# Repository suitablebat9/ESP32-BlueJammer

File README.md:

# ESP32-BlueJammer

**Bluetooth / BLE / WiFi / 2.4GHz Jamming Board**

The **ESP32-BlueJammer** is a compact, feature-rich board designed to disrupt devices operating on the 2.4GHz frequency band. Powered by an ESP32 and an nRF24 module, it generates noise and sends excessive packets to interfere with:

- Bluetooth audio and data connections  
- WiFi networks  
- BLE (Bluetooth Low Energy) devices  
- RC drones and remotes  
- IoT gadgets and more

> ⚠️ **Disclaimer:** This project is based entirely on the work of [Emensta](https://github.com/EmenstaNougat/ESP32-BlueJammer). I created this PCB to make their project more plug-and-play. All credit for the original firmware and research goes to them.

---

## 🔧 Features

- Toggleable on/off switch  
- Onboard momentary activation button  
- **`EXT Switch`** solder pads for external or wireless switch activation  
- **`EXT Power`** solder pads for external 5V power input  
  - (Polarity: **Left = GND**, **Right = 5V** with antennas facing away from you)  
- Combo firmware support – press the ESP32’s boot button while powered to cycle modes  
- **Blue jamming LED** shows active mode (can be disabled via jumper)  
- PH 2.0 battery connector (battery not included, connector provided)  
- USB Type-C power input on the board (not on the ESP32 directly)

---

## 🔄 LED Blink Mode Key

The **blue jamming LED** will blink to indicate the current active jamming mode on combo firmware:

- `1 blink` = **BT** (Bluetooth Classic)  
- `2 blinks` = **BLE** (Bluetooth Low Energy)  
- `3 blinks` = **WiFi**  
- `4 blinks` = **RC** (2.4GHz Drone/Remote)

The blink key is also printed on the right side of the board for quick reference.

---

## 🛰️ Mode Descriptions

| Mode               | Description                         | Frequency Range          |
|--------------------|-------------------------------------|--------------------------|
| **BT 80CH**        | Bluetooth Classic Jammer            | 2.402 – 2.480 GHz        |
| **BLE 40CH**       | Bluetooth Low Energy Jammer         | 2.400 – 2.4835 GHz       |
| **BT-BLE 40-80CH** | Classic BT + BLE Combo Jammer       | 2.400 – 2.4835 GHz       |
| **BT-WiFi 14-80CH**| Classic BT + WiFi Combo Jammer      | 2.400 – 2.4835 GHz       |
| **WiFi 14CH**      | WiFi Jammer                         | 2.400 – 2.4835 GHz       |
| **2.4GHz All**     | RC / Drone Jammer (CH 1–125)        | 2.400 – 2.525 GHz        |

---

## 🔌 Flashing the Firmware

You can easily flash your board using the browser-based [ESP32 BlueJammer Web Flasher](https://esp32-bluejammerflasher.pages.dev/) provided by Emensta.

### Steps:
1. Visit [ESP32-BlueJammerFlasher](https://esp32-bluejammerflasher.pages.dev/)
2. Choose the firmware type, "Generic"
3. Choose the firmware you want to flash
4. Connect your ESP32 via a data USB cable
5. Flash the firmware of your choice

> 💡 Tip: If flashing fails, make sure you’re using a data-capable USB cable and have the correct drivers installed for your ESP32.

---

## 🛒 Buy the Board

Want a fully assembled board? You can purchase one from my Tindie store here:  
👉 [PCB Studios on Tindie](https://www.tindie.com/products/pcb-studios/esp32-bluejammer/)

---

## 📦 What's Included

- Fully assembled **ESP32-BlueJammer PCB**
- PH 2.0 battery connector pre-installed
- Matching PH 2.0 connector for your battery (DIY soldering)
- Gerber files and schematic PDF (in this repo)

---

## ⚠️ Legal Notice

This project is for educational purposes only. Do not use this board to interfere with any wireless communications unless you have permission and are operating in a controlled, legal environment. You are solely responsible for what you do with this device.

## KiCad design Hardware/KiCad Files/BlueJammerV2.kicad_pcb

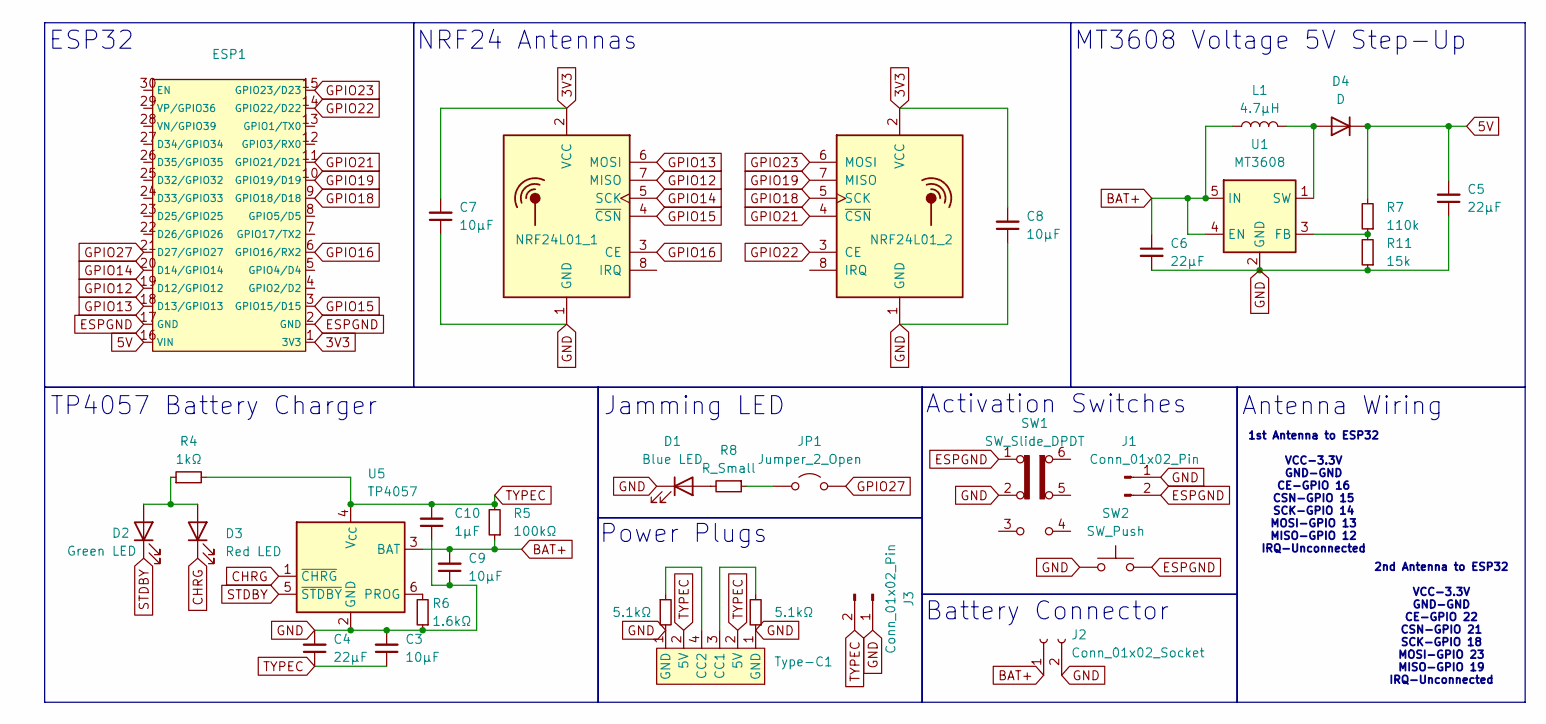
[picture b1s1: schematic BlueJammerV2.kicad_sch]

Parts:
C3, C7, C8, C9: 10µF; Cap_0805_2012Metric
C4, C5, C6: 22µF; Cap_0805_2012Metric
C10: 1µF; Cap_0805_2012Metric
D1: Blue LED; LED_1206_3216Metric_Pad1.42x1.75mm_HandSolder
D2: Green LED; LED_1206_3216Metric_Pad1.42x1.75mm_HandSolder
D3: Red LED; LED_1206_3216Metric_Pad1.42x1.75mm_HandSolder
D4: D; D_0805_2012Metric_Pad1.15x1.40mm_HandSolder
ESP1: 30 Pin ESP32 Dev Board
J1, J3: Conn_01x02_Pin; PinHeader_1x02_P2.54mm_Vertical
J2: Conn_01x02_Socket; JST_PH_S2B-PH-K_1x02_P2.00mm_Horizontal
JP1: Jumper_2_Open; TestPoint_2Pads_Pitch2.54mm_Drill0.8mm
L1: 4.7µH; L_0805_2012Metric_Pad1.15x1.40mm_HandSolder
R4: 1kΩ; R_1206_3216Metric
R5: 100kΩ; R_1206_3216Metric
R6: 1.6kΩ; R_1206_3216Metric
R7: 110k; R_0805_2012Metric_Pad1.20x1.40mm_HandSolder
R8: R_Small; R_1206_3216Metric
R9, R10: 5.1kΩ; R_1206_3216Metric
R11: 15k; R_0805_2012Metric_Pad1.20x1.40mm_HandSolder
SW1: SW_Slide_DPDT; MSS-22D18 Slide Switch
SW2: SW_Push; Button
Type-C1: SMD Type-C Port
U1: MT3608; SOT-23-6_Handsoldering
U2: NRF24L01_1; nRF24L01_Breakout
U3: NRF24L01_2; nRF24L01_Breakout
U5: TP4057; TSOT-23-6_HandSoldering

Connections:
3V3: C7.2, C8.2, ESP1.1 (3V3), U2.2 (VCC), U3.2 (VCC)
5V: C5.2, D4.1 (K), ESP1.16 (VIN), R7.2
BAT+: C6.1, C9.2, J2.1, L1.1, R5.1, U1.4 (EN), U1.5 (IN), U5.3 (BAT)
CHRG: D3.1 (K), U5.1 (~CHRG)
ESPGND: ESP1.2 (GND), ESP1.17 (GND), J1.2, SW1.1 (A), SW2.2
GND: C3.2, C4.2, C5.1, C6.2, C7.1, C8.1, C9.1, C10.1, D1.1 (K), J1.1, J2.2, J3.1, R6.1, R9.1, R10.2, R11.1, SW1.2 (B), SW2.1, Type-C1.1 (GND), U1.2 (GND), U2.1 (GND), U3.1 (GND), U5.2 (GND)
GPIO12: ESP1.19 (D12/GPIO12), U2.7 (MISO)
GPIO13: ESP1.18 (D13/GPIO13), U2.6 (MOSI)
GPIO14: ESP1.20 (D14/GPIO14), U2.5 (SCK)
GPIO15: ESP1.3 (GPIO15/D15), U2.4 (~CSN)
GPIO16: ESP1.6 (GPIO16/RX2), U2.3 (CE)
GPIO18: ESP1.9 (GPIO18/D18), U3.5 (SCK)
GPIO19: ESP1.10 (GPIO19/D19), U3.7 (MISO)
GPIO21: ESP1.11 (GPIO21/D21), U3.4 (~CSN)
GPIO22: ESP1.14 (GPIO22/D22), U3.3 (CE)
GPIO23: ESP1.15 (GPIO23/D23), U3.6 (MOSI)
GPIO27: ESP1.21 (D27/GPIO27), JP1.2 (B)
unnamed: D1.2 (A), R8.2
unnamed: D2.2 (A), D3.2 (A), R4.1
unnamed: D4.2 (A), L1.2, U1.1 (SW)
unnamed: JP1.1 (A), R8.1
unnamed: R9.2, Type-C1.3 (CC1)
unnamed: R10.1, Type-C1.4 (CC2)
unnamed: R7.1, R11.2, U1.3 (FB)
unnamed: R6.2, U5.6 (PROG)
STDBY: D2.1 (K), U5.5 (~STDBY)
TYPEC: C3.1, C4.1, C10.2, J3.2, R4.2, R5.2, Type-C1.2 (5V), U5.4 (V_{CC})

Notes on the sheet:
Jamming LED
1st Antenna to ESP32 VCC-3.3V GND-GND CE-GPIO 16 CSN-GPIO 15 SCK-GPIO 14 MOSI-GPIO 13 MISO-GPIO 12 IRQ-Unconnected
MT3608 Voltage 5V Step-Up
Power Plugs
ESP32
Activation Switches
TP4057 Battery Charger
NRF24 Antennas
Battery Connector
2nd Antenna to ESP32 VCC-3.3V GND-GND CE-GPIO 22 CSN-GPIO 21 SCK-GPIO 18 MOSI-GPIO 23 MISO-GPIO 19 IRQ-Unconnected
Antenna Wiring

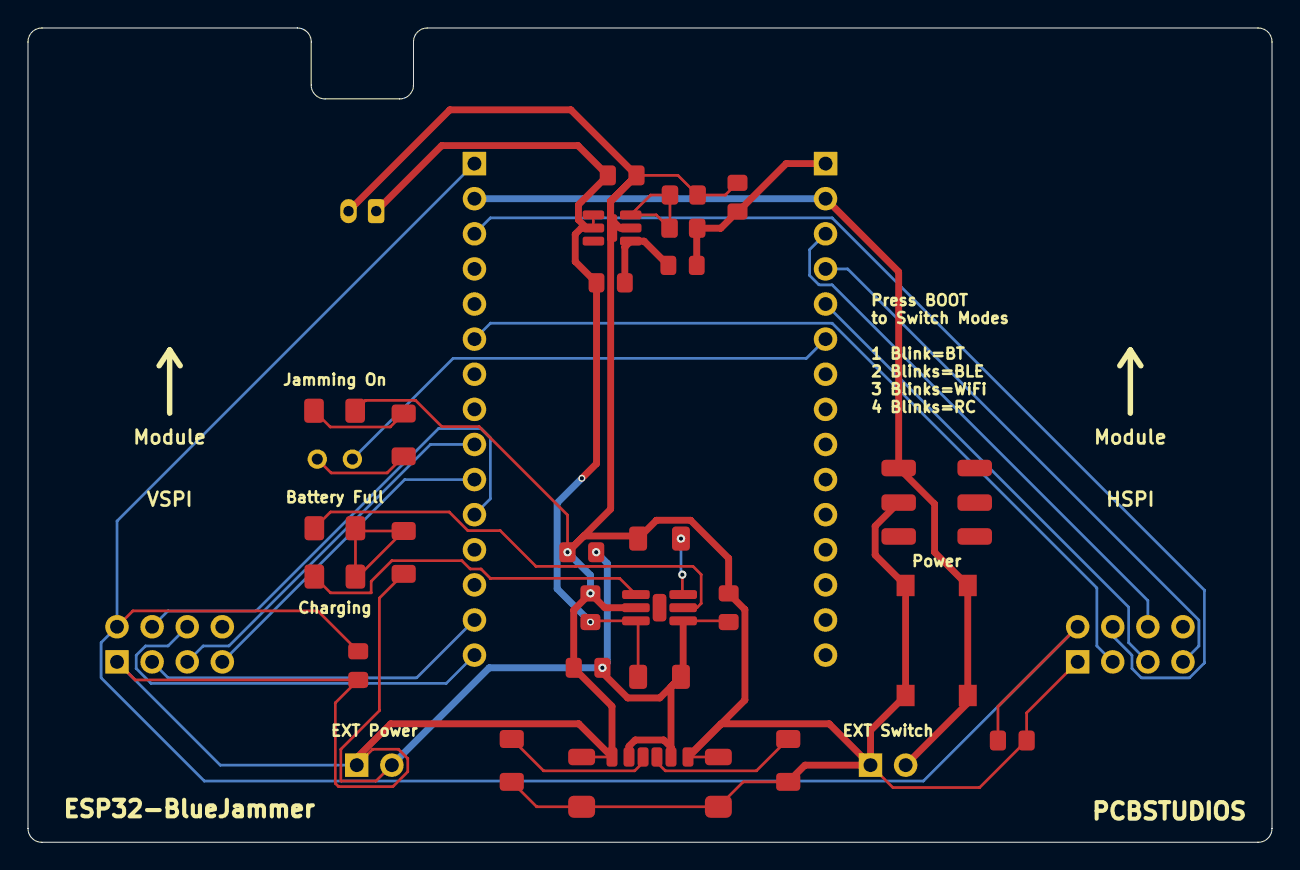
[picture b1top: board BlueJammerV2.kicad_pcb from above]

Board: 2 copper layers, 90.0 x 58.9 mm, 33 parts (0 on the bottom side), 27 nets.

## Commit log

2025-05-25 Create temp
